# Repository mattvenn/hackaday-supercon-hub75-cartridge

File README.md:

# hub75E cartridge for hackaday supercon 2019 badge

[schematic pdf](schematic.pdf)

based off

* https://github.com/Spritetm/hadbadge2019_protoboard
* https://github.com/icebreaker-fpga/icebreaker-pmod/blob/master/led-panel/v1.2c/led-panel-sch.pdf

checked pin polarity of 3.3v with sprite_tm.

apologies for using kicad4.

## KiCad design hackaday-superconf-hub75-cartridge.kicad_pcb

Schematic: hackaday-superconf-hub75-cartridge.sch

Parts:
C1: C; C_0805_HandSoldering
J1: Conn_02x06_Odd_Even; Socket_Strip_Angled_2x06_Pitch2.54mm; farnell # 1593452
J2: Conn_02x20_Odd_Even; Pin_Header_Angled_2x20_Pitch2.54mm; farnell # 2847214
J3: Conn_02x08_Odd_Even; Pin_Header_Straight_2x08_Pitch2.54mm; farnell # 2843530
J4: Conn_01x01; Pin_Header_Straight_1x01_Pitch2.54mm
U1: S25FL208K; SOIJ-8_5.3x5.3mm_Pitch1.27mm; farnell # 2340553

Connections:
+3V3: C1.1, J1.1, J1.2, J2.1, U1.8 (VCC)
/a0: J2.15, J3.9
/a1: J2.14, J3.10
/a2: J2.13, J3.11
/a3: J2.12, J3.12
/b0: J2.21, J3.3
/b1: J2.17, J3.7
/blank: J2.9, J3.15
/clk: J2.11, J3.13
/cs: J2.3, U1.1 (S#)
/g0: J2.18, J3.2
/g1: J2.16, J3.6
/hold: J2.4, U1.7 (HOLD#)
/latch: J2.10, J3.14
/miso: J2.5, U1.2 (DQ1)
/mosi: J2.8, U1.5 (DQ0)
/pm1: J1.12, J2.32
/pm2: J1.10, J2.30
/pm3: J1.8, J2.28
/pm4: J1.6, J2.26
/pm7: J1.11, J2.31
/pm8: J1.9, J2.29
/pm9: J1.7, J2.27
/pm10: J1.5, J2.25
/r0: J2.23, J3.1
/r1: J2.19, J3.5
/sck: J2.6, U1.6 (C)
/wp: J2.7, U1.3 (W#/VPP)
GND: C1.2, J1.3, J1.4, J2.2, J3.4, J3.16, U1.4 (VSS)
unnamed: J3.8, J4.1

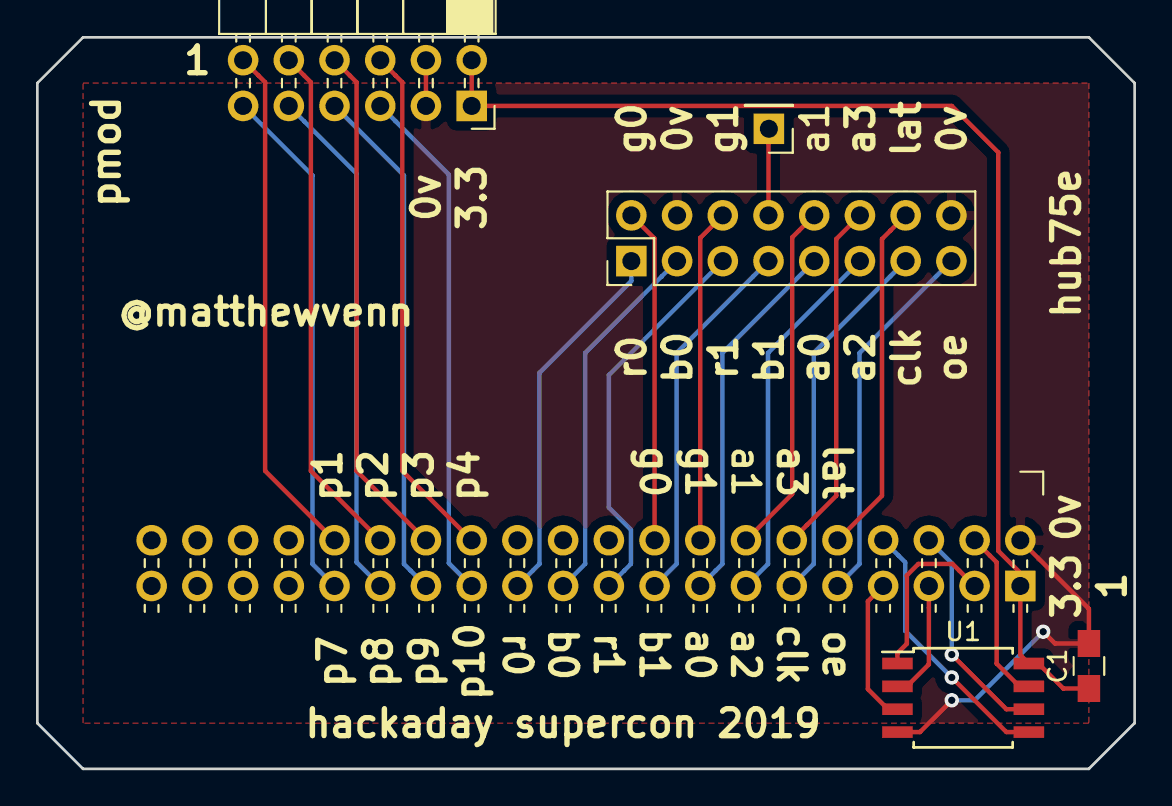
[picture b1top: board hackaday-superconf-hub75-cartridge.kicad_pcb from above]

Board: 2 copper layers, 61.0 x 40.6 mm, 6 parts (0 on the bottom side), 30 nets.

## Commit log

2019-11-05 schematic and png
2019-11-05 readme
2019-11-05 added farnell part nums
